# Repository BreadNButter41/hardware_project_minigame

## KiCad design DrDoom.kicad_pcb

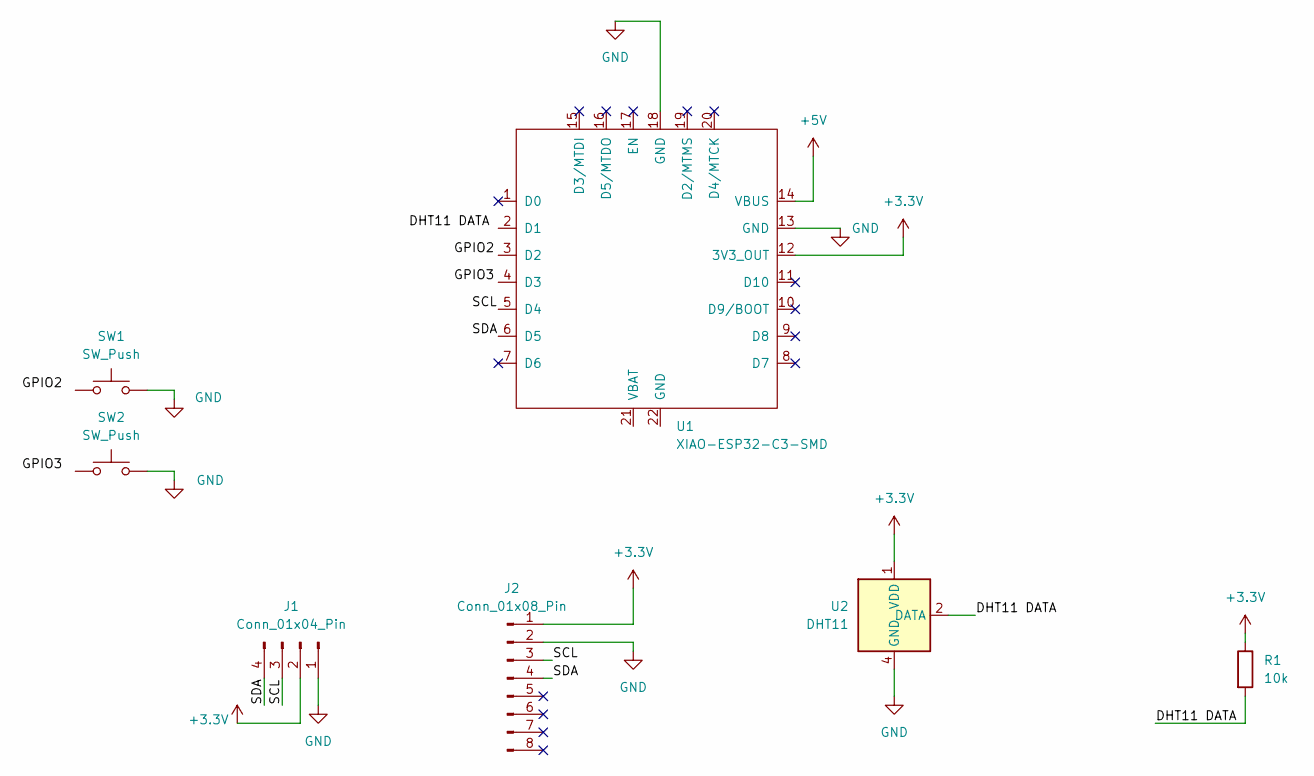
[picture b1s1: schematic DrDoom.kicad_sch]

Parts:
J1: Conn_01x04_Pin; Display_128x64_096_I2C
J2: Conn_01x08_Pin; PinHeader_1x08_P2.54mm_Vertical
R1: 10k; R_Axial_DIN0204_L3.6mm_D1.6mm_P7.62mm_Horizontal
SW1, SW2: SW_Push; SW_Cherry_MX_1.00u_PCB
U1: XIAO-ESP32-C3-SMD
U2: DHT11; Aosong_DHT11_5.5x12.0_P2.54mm

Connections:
+3.3V: J1.2, J2.1, R1.1, U1.12 (3V3_OUT), U2.1 (VDD)
+5V: U1.14 (VBUS)
/DHT11 DATA: R1.2, U2.2 (DATA)
/SCL: J1.3, J2.3
/SDA: J1.4, J2.4
GND: J1.1, J2.2, SW1.2 (2_2), SW2.2 (2_2), U1.13 (GND), U1.18 (GND), U2.4 (GND)

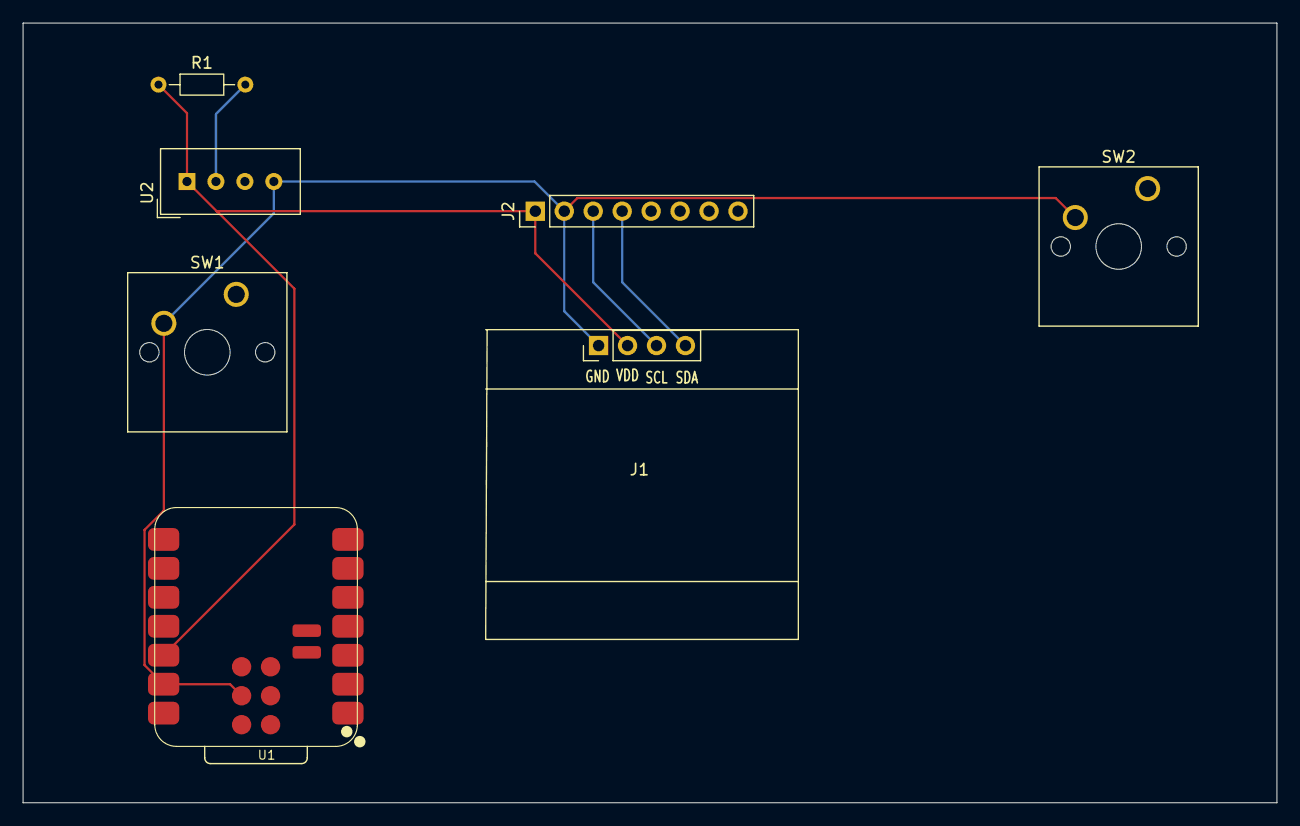
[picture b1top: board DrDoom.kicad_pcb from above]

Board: 2 copper layers, 110.0 x 68.4 mm, 7 parts (0 on the bottom side), 5 nets.
